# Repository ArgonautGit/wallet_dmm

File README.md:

# wallet_dmm

A multimeter the size of a credit card: DC volts, resistance, continuity and
diode test, shown on a 0.91" OLED, with three buttons, an RGB LED and a piezo
beeper. It runs from a small LiPo that charges over USB-C and is built around
an STM32L051K8, with Rust firmware and a simulation of the whole thing.

This is revision 3. Rev 1 (the October 2024 JLCPCB order) is commit `a01ea68`;
rev 2 is the `v2` branch.

| | |
|---|---|
| Inputs | COM, V (10 MΩ) and Ω (resistance, continuity, diode) on a 2.54 mm header |
| Voltage | −30 V to +31 V; negative readings through a 1.55 V mid-rail bias |
| Resistance | 0–200 kΩ against a 0.1 % 10 kΩ reference, 150 kΩ–10 MΩ against 1 MΩ, autoranging |
| Continuity, diode | 0.3 mA test current, open-circuit 3.0 V |
| Overload | both inputs survive ±30 V DC; not for mains or anything above 30 V |
| Power | 3.7 V LiPo (protected cell), 100 mA USB-C charging, 3.0 V rail, about 5 µA off |
| Board | 85.6 × 54 mm (ID-1 card), 2 layers, 0.8 mm FR4 |

## Changes from rev 1 and rev 2

- **Power.** The CR1025 (rated 0.1 mA continuous) could not run an OLED. It is
  replaced by a LiPo charged from USB-C (MCP73831), a 1 µA 3.0 V LDO that
  stays on while the MCU sleeps in Stop mode, a slide switch that disconnects
  the battery, bulk decoupling, and a load switch (Q1/Q2) that cuts the OLED
  module's supply.
- **Piezo.** The always-running 555 and its two MOSFETs are gone. The MCU
  drives the piezo push-pull from TIM22 CH1/CH2 on PB4/PB5, which gives
  6 Vp-p from 3 V and draws nothing when silent.
- **Programming.** SWD is on PA13/PA14 with NRST, with nothing else on those
  pins. USART1 (PA9/PA10, also the ROM bootloader) is on test pads.
- **Measurement.** Separate V and Ω inputs. The V input is a 9.87 MΩ divider
  biased to a mid-rail reference, with a hold capacitor because the ADC wants
  a source below 50 kΩ. The Ω input has two reference ranges; its drive nodes
  are clamped to ground and the battery, so a voltage on it pushes at most
  2.5 mA into the cell instead of into the MCU or the 3.0 V rail. What the
  MCU pins' own clamps still pass would lift the rail while the MCU sleeps
  (the LDO cannot sink current), so a TL431 (U4) holds it below 3.32 V.
- **Everything else.** A resistor for each LED colour, with the anode on the
  battery so green and blue have headroom. The MCU's calibrated internal
  sensor replaces the TO-92 MCP9700. Decoupling sits at the pins. Every part
  is stocked by JLCPCB and carries its LCSC number. All libraries are in the
  repo.

## Layout of the repository

- `hardware/`: KiCad 10 project (schematic, board, project rules, footprints
  for the RGB LED and the OLED module, 3D models for every part)
- `scripts/`: generators for the schematic, board and 3D models, the
  autorouter wrapper, the fab-file export and the renders
- `fab/`: Gerbers, drill files, BOM and pick-and-place for JLCPCB, schematic
  and assembly PDFs
- `firmware/`: Rust firmware and its simulation (see
  [firmware/README.md](firmware/README.md))
- `docs/`: renders of the board and the simulation results

## Building

Everything runs in the dev shell (`nix develop`, or direnv).

```sh
./scripts/build.sh          # schematic -> ERC -> board -> DRC -> fab/
```

The schematic and board are generated by `scripts/gen_schematic.py` and
`scripts/gen_pcb.py`; edit those rather than the KiCad files, or the next
build will overwrite the change. Tracks come from `hardware/routes.json`.
After moving parts or changing the netlist, route again with Freerouting:

```sh
kicad-cli sch export netlist --format kicadsexpr -o build/wallet_dmm.net hardware/wallet_dmm.kicad_sch
python3 scripts/autoroute.py build/wallet_dmm.net
```

The build stops on any ERC or DRC error and checks that the board matches the
schematic.

The renders in `docs/renders/` and a GLB of the populated board
(`build/wallet_dmm.glb`, for any glTF viewer) come from:

```sh
./scripts/render.sh
```

Most parts use KiCad's own 3D models; the switches, buzzer, USB-C socket and
RGB LED use the manufacturers' models (via EasyEDA). The OLED module and the
battery are drawn by `scripts/gen_models.py`, which lights the OLED's pixels
with the firmware's volts screen:

```sh
nix develop .#models -c uv run --with cadquery python scripts/gen_models.py
```

## Ordering from JLCPCB

Upload `fab/wallet_dmm-gerbers.zip`: 2 layers, **0.8 mm**, 1 oz, any colour,
HASL lead-free or ENIG. For assembly, choose top side and upload
`fab/bom-jlcpcb.csv` and `fab/cpl-jlcpcb.csv`. In the placement preview,
check the orientation of U1 (pin 1 dot), U2, U3, Q1, Q2, D2, D3, D1 (cathode)
and D4 (anode corner, the dot in the silkscreen) before confirming.

Solder these by hand afterwards:

- J3: a 0.91" 128×32 SSD1306 I2C module, flat on the board, header pins cut
  short. Match the module's pin labels to the silkscreen (GND VCC SCL SDA).
- J2: a 3-pin header or the probe leads (COM, V, Ω).
- J5: the battery wires from the back, BAT+ to the square pad.
- J4 stays empty; hold a header in it for an ST-Link, or solder one while
  developing.

## Battery

A LiPo pouch cell with its own protection circuit, up to 30 × 40 × 4 mm,
taped to the marked area on the back (no pins poke through there). Charging
runs at 100 mA, so use 150 mAh or more; R3 sets the current (1000 V / R3).

## Bring-up

1. Before connecting anything, check that BAT and 3V0 (TP3, TP4) are not
   shorted to GND.
2. Connect the battery and slide SW5 to ON. TP4 reads 2.94–3.06 V. If it
   reads 0 V, the switch is the other way round from the silkscreen: fix the
   labels in `scripts/gen_pcb.py`.
3. Plug in USB-C: the CHG LED lights while the cell charges and goes out when
   it is full.
4. Flash over SWD (ST-Link on J4: 3V0, SWDIO, SWCLK, NRST, GND). Holding
   RESET while connecting works if firmware has put the MCU to sleep.
5. With the firmware running ([firmware/README.md](firmware/README.md)):
   short V to COM in DC V and hold C for 3 s to store the zero; do the same
   with the Ω leads in Ω mode. Then put 5–30 V on the V input, measure it with another
   meter, and send `cal <volts>` over the UART (TP2) to set the gain.

## Firmware

The firmware is in [firmware/](firmware/): Rust and Embassy, with all the
maths and the UI in a host-tested crate. Its README covers the buttons,
calibration, flashing and the simulation. The pins:

| Pin | Use |
|---|---|
| PA0 ADC_IN0 | E_LO: the low-range drive node, through R18 |
| PA1 ADC_IN1 | VMID, the bias under the V divider |
| PA2 | VMID_EN: high while measuring volts |
| PA3 | OHM_HI: high-range drive (1 MΩ), analog otherwise |
| PA4 ADC_IN4 | V input divider |
| PA5 ADC_IN5 | Ω input, through R21 into C13 |
| PA6 | OHM_LO: low-range drive (10 kΩ), analog otherwise |
| PA7 | VBUS present (high on USB) |
| PB1 ADC_IN9 | switched battery ÷ 2 |
| PA8, PA15, PB3 | LED blue, red, green (low = on; PA15/PB3 are TIM2 CH1/CH2) |
| PB4, PB5 | piezo, TIM22 CH1/CH2 in antiphase, about 4 kHz |
| PB6, PB7 | I2C1 to the OLED (address 0x3C) |
| PC15 | OLED power: high = on |
| PA11, PA12, PC14 | buttons A, B, C to GND (enable pull-ups) |
| PA9, PA10 | USART1 TX/RX on TP1/TP2 |

## Simulation

`firmware/simulate.sh` runs the front end in ngspice, feeds it through a
model of the ADC into the firmware's own maths, and runs the release binary
in Renode on an emulated STM32L051. Across 200 simulated boards with 1 %
parts, calibrated volts are within ±4 mV up to ±5 V and ±33 mV at ±30 V,
and ohms within ±0.34 % from 1 kΩ to 100 kΩ. The details and plots are in
[firmware/README.md](firmware/README.md#simulation) and
[docs/simulation/](docs/simulation/).

## Renders

| Front | Back, with the battery |
|---|---|
|  |  |

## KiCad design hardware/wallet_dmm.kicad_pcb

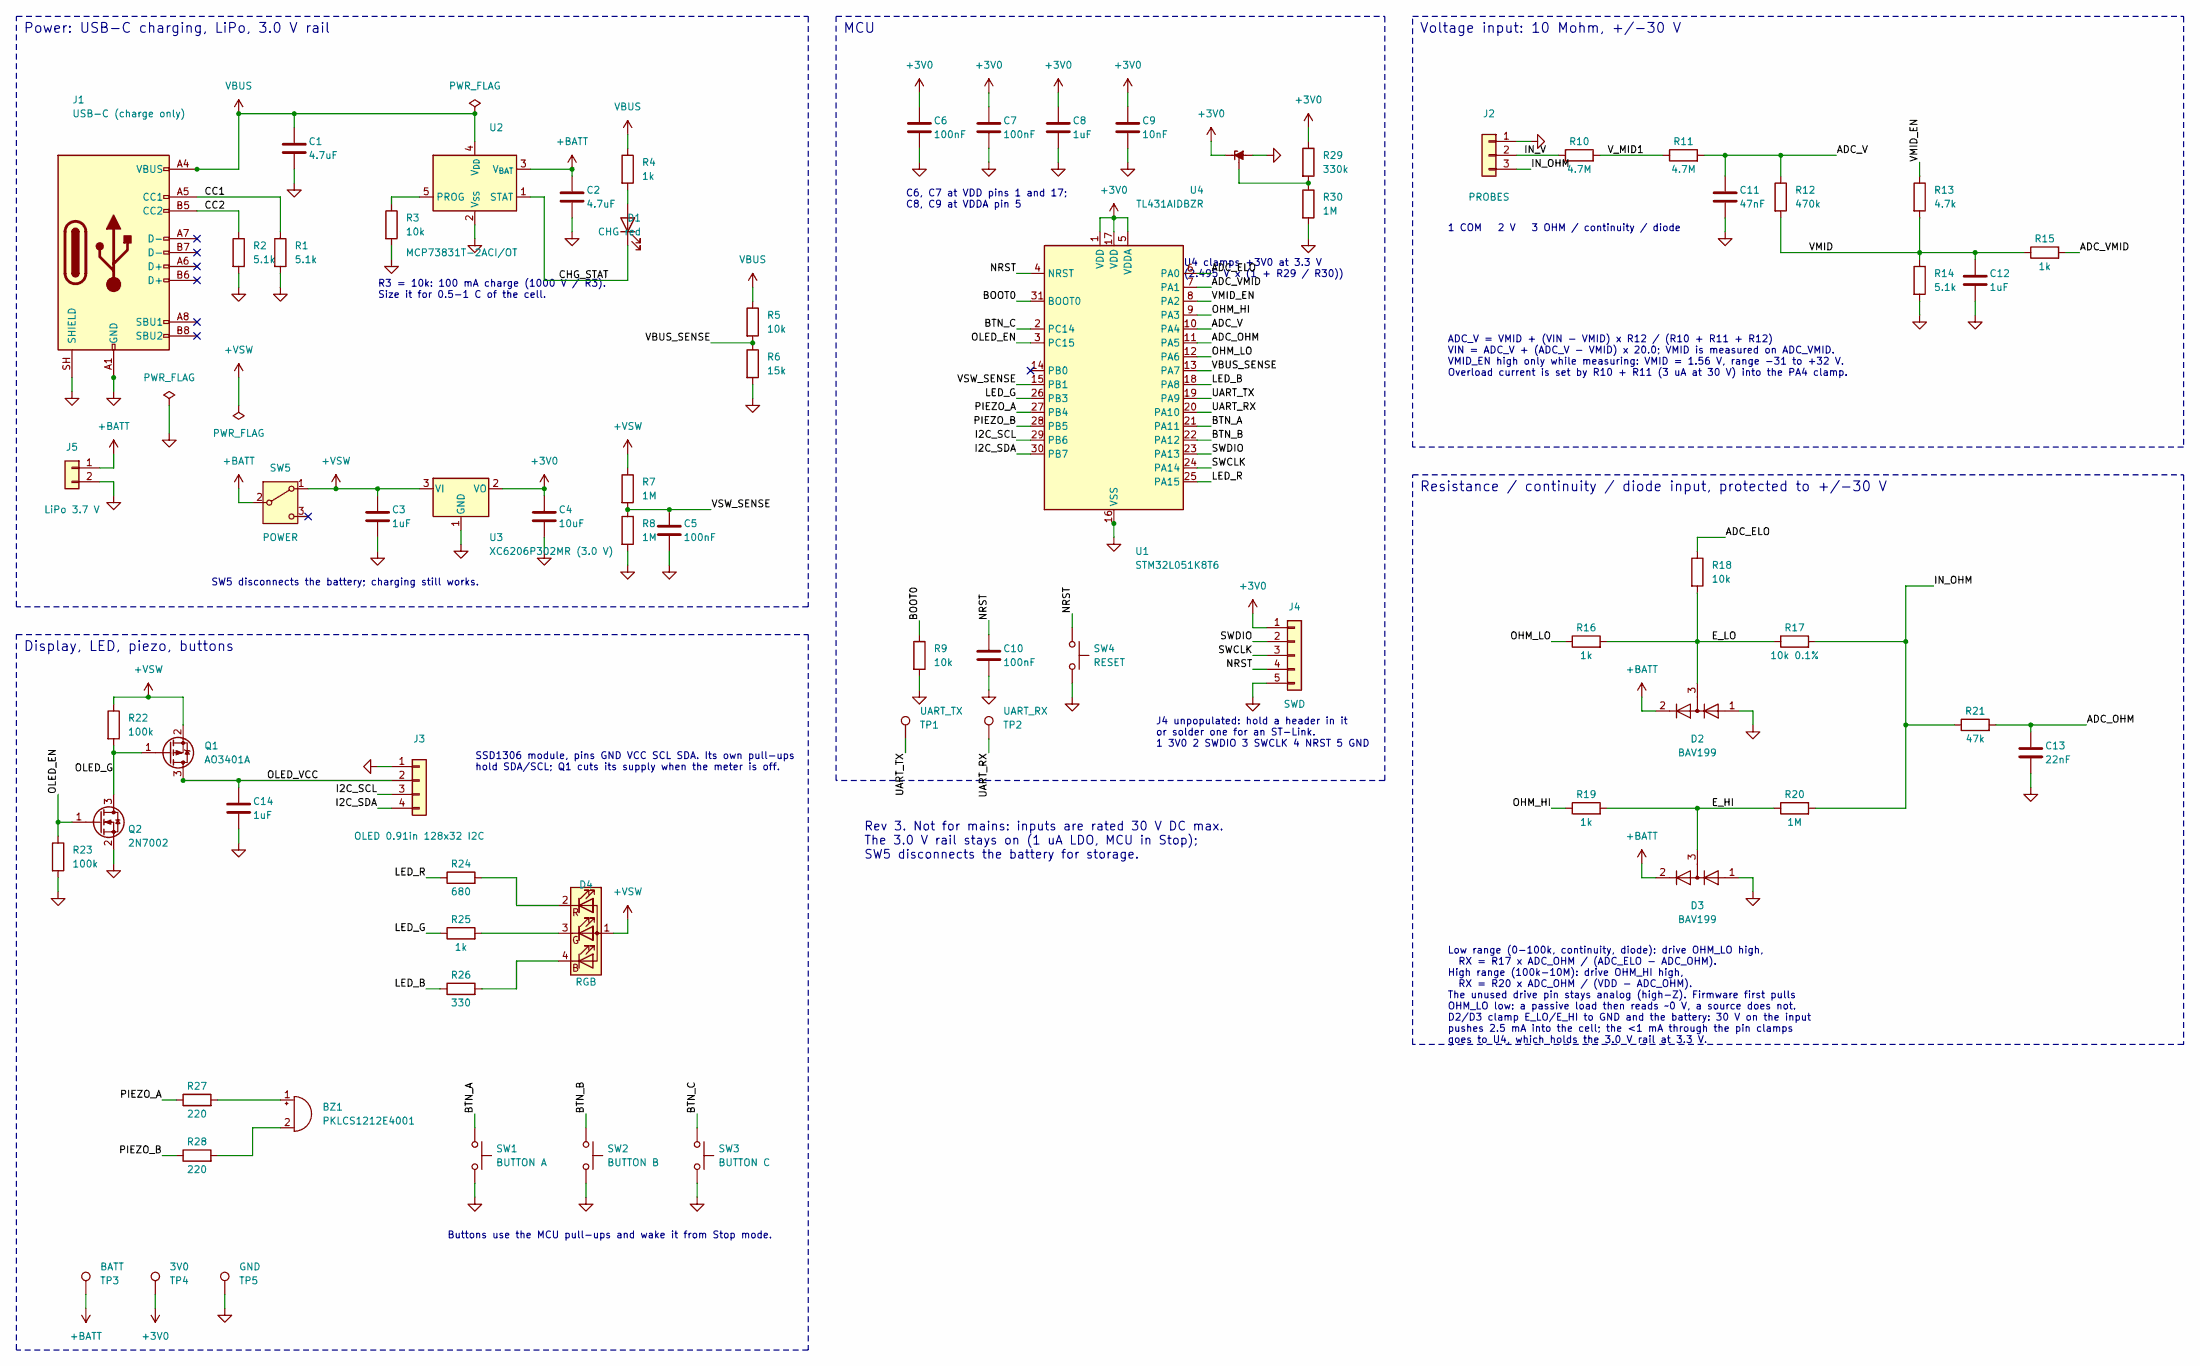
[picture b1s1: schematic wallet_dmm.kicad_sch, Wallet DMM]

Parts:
BZ1: PKLCS1212E4001; Buzzer_Murata_PKLCS1212E; MPN PKLCS1212E4001-R1; LCSC C113159
C1, C2: 4.7uF; C_0603_1608Metric; MPN CL10A475KO8NNNC; LCSC C19666
C3, C8, C12, C14: 1uF; C_0603_1608Metric; MPN CL10A105KB8NNNC; LCSC C15849
C4: 10uF; C_0603_1608Metric; MPN CL10A106KP8NNNC; LCSC C19702
C5, C6, C7, C10: 100nF; C_0603_1608Metric; MPN CC0603KRX7R9BB104; LCSC C14663
C9: 10nF; C_0603_1608Metric; MPN 0603B103K500NT; LCSC C57112
C11: 47nF; C_0603_1608Metric; MPN CL10B473KB8NNNC; LCSC C1622
C13: 22nF; C_0603_1608Metric; MPN CL10B223KB8NNNC; LCSC C21122
D1: CHG red; LED_0603_1608Metric; MPN KT-0603R; LCSC C2286
D2, D3: BAV199; SOT-23; MPN BAV199,215; LCSC C40919
D4: RGB; LED_RGB_1615_CA; MPN TJ-S1615CY6TGLCCYRGB-A5; LCSC C601683
J1: USB-C (charge only); USB_C_Receptacle_HRO_TYPE-C-31-M-12; MPN TYPE-C-31-M-12; LCSC C165948
J2: PROBES; PinHeader_1x03_P2.54mm_Vertical
J3: OLED 0.91in 128x32 I2C; OLED_0.91in_128x32_Module
J4: SWD; PinHeader_1x05_P2.54mm_Vertical
J5: LiPo 3.7 V; SolderWire-0.25sqmm_1x02_P4.5mm_D0.65mm_OD2mm
Q1: AO3401A; SOT-23; MPN AO3401A; LCSC C15127
Q2: 2N7002; SOT-23; MPN 2N7002; LCSC C8545
R1, R2, R14: 5.1k; R_0603_1608Metric; MPN 0603WAF5101T5E; LCSC C23186
R3, R5, R9, R18: 10k; R_0603_1608Metric; MPN 0603WAF1002T5E; LCSC C25804
R4, R15, R16, R19, R25: 1k; R_0603_1608Metric; MPN 0603WAF1001T5E; LCSC C21190
R6: 15k; R_0603_1608Metric; MPN 0603WAF1502T5E; LCSC C22809
R7, R8, R20, R30: 1M; R_0603_1608Metric; MPN 0603WAF1004T5E; LCSC C22935
R10, R11: 4.7M; R_1206_3216Metric; MPN 1206W4F4704T5E; LCSC C37800
R12: 470k; R_0603_1608Metric; MPN 0603WAF4703T5E; LCSC C23178
R13: 4.7k; R_0603_1608Metric; MPN 0603WAF4701T5E; LCSC C23162
R17: 10k 0.1%; R_1206_3216Metric; MPN RT1206BRD0710KL; LCSC C136889
R21: 47k; R_0603_1608Metric; MPN 0603WAF4702T5E; LCSC C25819
R22, R23: 100k; R_0603_1608Metric; MPN 0603WAF1003T5E; LCSC C25803
R24: 680; R_0603_1608Metric; MPN 0603WAF6800T5E; LCSC C23228
R26: 330; R_0603_1608Metric; MPN 0603WAF3300T5E; LCSC C23138
R27, R28: 220; R_0603_1608Metric; MPN 0603WAF2200T5E; LCSC C22962
R29: 330k; R_0603_1608Metric; MPN 0603WAF3303T5E; LCSC C23137
SW1: BUTTON A; SW_Push_1P1T_XKB_TS-1187A; MPN TS-1187A-B-A-B; LCSC C318884
SW2: BUTTON B; SW_Push_1P1T_XKB_TS-1187A; MPN TS-1187A-B-A-B; LCSC C318884
SW3: BUTTON C; SW_Push_1P1T_XKB_TS-1187A; MPN TS-1187A-B-A-B; LCSC C318884
SW4: RESET; SW_Push_1P1T_XKB_TS-1187A; MPN TS-1187A-B-A-B; LCSC C318884
SW5: POWER; SW_SPDT_Shouhan_MSK12C02; MPN MSK12C02; LCSC C431540
TP1: UART_TX; TestPoint_Pad_D1.5mm
TP2: UART_RX; TestPoint_Pad_D1.5mm
TP3: BATT; TestPoint_Pad_D1.5mm
TP4: 3V0; TestPoint_Pad_D1.5mm
TP5: GND; TestPoint_Pad_D1.5mm
U1: STM32L051K8T6; LQFP-32_7x7mm_P0.8mm; MPN STM32L051K8T6; LCSC C915970
U2: MCP73831T-2ACI/OT; SOT-23-5; MPN MCP73831T-2ACI/OT; LCSC C424093
U3: XC6206P302MR (3.0 V); SOT-23-3; MPN XC6206P302MR-G; LCSC C9972
U4: TL431AIDBZR; SOT-23; MPN TL431AIDBZR; LCSC C23892

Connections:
+3V0: C4.1, C6.1, C7.1, C8.1, C9.1, J4.1, R29.1, TP4.1, U1.1 (VDD), U1.5 (VDDA), U1.17 (VDD), U3.2 (VO), U4.1 (K)
+BATT: C2.1, D2.2 (A), D3.2 (A), J5.1, SW5.2 (B), TP3.1, U2.3 (V_{BAT})
+VSW: C3.1, D4.1 (A), Q1.2 (S), R7.1, R22.1, SW5.1 (A), U3.3 (VI)
/ADC_ELO: R18.1, U1.6 (PA0)
/ADC_OHM: C13.1, R21.2, U1.11 (PA5)
/ADC_V: C11.1, R11.2, R12.1, U1.10 (PA4)
/ADC_VMID: R15.2, U1.7 (PA1)
/BOOT0: R9.1, U1.31 (BOOT0)
/BTN_A: SW1.1, U1.21 (PA11)
/BTN_B: SW2.1, U1.22 (PA12)
/BTN_C: SW3.1, U1.2 (PC14)
/CC1: J1.A5 (CC1), R1.1
/CC2: J1.B5 (CC2), R2.1
/CHG_STAT: D1.1 (K), U2.1 (STAT)
/E_HI: D3.3 (K), R19.2, R20.1
/E_LO: D2.3 (K), R16.2, R17.1, R18.2
/I2C_SCL: J3.3, U1.29 (PB6)
/I2C_SDA: J3.4, U1.30 (PB7)
/IN_OHM: J2.3, R17.2, R20.2, R21.1
/IN_V: J2.2, R10.1
/LED_B: R26.1, U1.18 (PA8)
/LED_G: R25.1, U1.26 (PB3)
/LED_R: R24.1, U1.25 (PA15)
/NRST: C10.1, J4.4, SW4.1, U1.4 (NRST)
/OHM_HI: R19.1, U1.9 (PA3)
/OHM_LO: R16.1, U1.12 (PA6)
/OLED_EN: Q2.1 (G), R23.1, U1.3 (PC15)
/OLED_G: Q1.1 (G), Q2.3 (D), R22.2
/OLED_VCC: C14.1, J3.2, Q1.3 (D)
/PIEZO_A: R27.1, U1.27 (PB4)
/PIEZO_B: R28.1, U1.28 (PB5)
/SWCLK: J4.3, U1.24 (PA14)
/SWDIO: J4.2, U1.23 (PA13)
/UART_RX: TP2.1, U1.20 (PA10)
/UART_TX: TP1.1, U1.19 (PA9)
/VBUS_SENSE: R5.2, R6.1, U1.13 (PA7)
/VMID: C12.1, R12.2, R13.2, R14.1, R15.1
/VMID_EN: R13.1, U1.8 (PA2)
/VSW_SENSE: C5.1, R7.2, R8.1, U1.15 (PB1)
/V_MID1: R10.2, R11.1
GND: C1.2, C2.2, C3.2, C4.2, C5.2, C6.2, C7.2, C8.2, C9.2, C10.2, C11.2, C12.2, C13.2, C14.2, D2.1 (K), D3.1 (K), J1.A1 (GND), J1.A12 (GND), J1.B1 (GND), J1.B12 (GND), J1.SH (SHIELD), J2.1, J3.1, J4.5, J5.2, Q2.2 (S), R1.2, R2.2, R3.2, R6.2, R8.2, R9.2, R14.2, R23.2, R30.2, SW1.2, SW2.2, SW3.2, SW4.2, TP5.1, U1.16 (VSS), U1.32 (VSS), U2.2 (V_{SS}), U3.1 (GND), U4.3 (A)
unnamed: BZ1.1 (+), R27.2
unnamed: BZ1.2 (-), R28.2
unnamed: D1.2 (A), R4.2
unnamed: D4.4 (BK), R26.2
unnamed: D4.3 (GK), R25.2
unnamed: D4.2 (RK), R24.2
unnamed: R3.1, U2.5 (PROG)
unnamed: R29.2, R30.1, U4.2 (REF)
VBUS: C1.1, J1.A4 (VBUS), J1.A9 (VBUS), J1.B4 (VBUS), J1.B9 (VBUS), R4.1, R5.1, U2.4 (V_{DD})

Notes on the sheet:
ADC_V = VMID + (VIN - VMID) x R12 / (R10 + R11 + R12) VIN = ADC_V + (ADC_V - VMID) x 20.0; VMID is measured on ADC_VMID. VMID_EN high only while measuring: VMID = 1.56 V, range -31 to +32 V. Overload current is set by R10 + R11 (3 uA at 30 V) into the PA4 clamp.
C6, C7 at VDD pins 1 and 17; C8, C9 at VDDA pin 5
J4 unpopulated: hold a header in it or solder one for an ST-Link. 1 3V0 2 SWDIO 3 SWCLK 4 NRST 5 GND
Power: USB-C charging, LiPo, 3.0 V rail
Voltage input: 10 Mohm, +/-30 V
R3 = 10k: 100 mA charge (1000 V / R3). Size it for 0.5-1 C of the cell.
Buttons use the MCU pull-ups and wake it from Stop mode.
Display, LED, piezo, buttons
Resistance / continuity / diode input, protected to +/-30 V
SSD1306 module, pins GND VCC SCL SDA. Its own pull-ups hold SDA/SCL; Q1 cuts its supply when the meter is off.
Rev 3. Not for mains: inputs are rated 30 V DC max. The 3.0 V rail stays on (1 uA LDO, MCU in Stop); SW5 disconnects the battery for storage.
Low range (0-100k, continuity, diode): drive OHM_LO high, RX = R17 x ADC_OHM / (ADC_ELO - ADC_OHM). High range (100k-10M): drive OHM_HI high, RX = R20 x ADC_OHM / (VDD - ADC_OHM). The unused drive pin stays analog (high-Z). Firmware first pulls OHM_LO low: a passive load then reads ~0 V, a source d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
SW5 disconnects the battery; charging still works.
1 COM 2 V 3 OHM / continuity / diode
U4 clamps +3V0 at 3.3 V (2.495 V x (1 + R29 / R30))
MCU

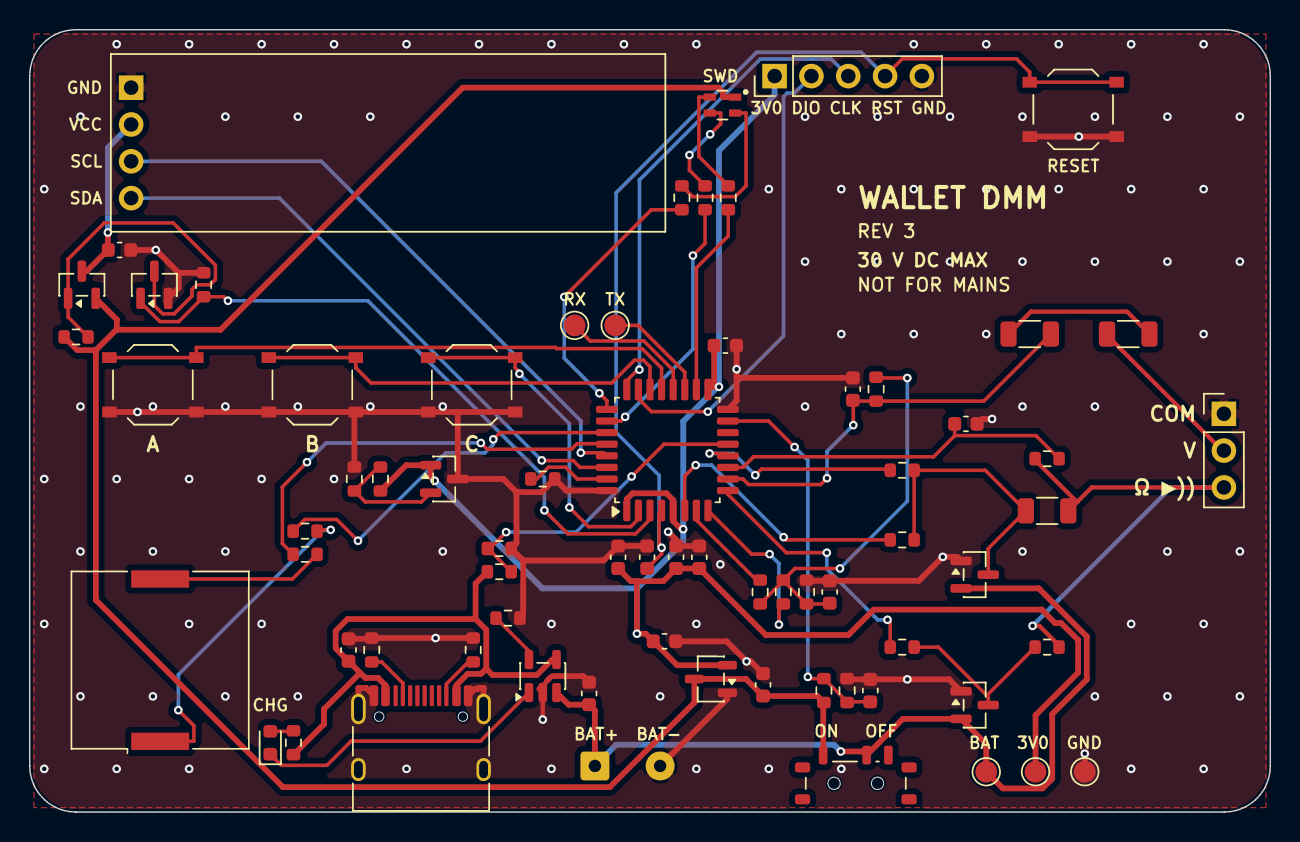
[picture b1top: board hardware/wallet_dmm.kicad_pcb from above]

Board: 2 copper layers, 85.6 x 54.0 mm, 70 parts (0 on the bottom side), 50 nets.

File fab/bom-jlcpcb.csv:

Comment,Designator,Footprint,LCSC Part #
PKLCS1212E4001,BZ1,Buzzer_Murata_PKLCS1212E,C113159
4.7uF,"C1,C2",C_0603_1608Metric,C19666
1uF,"C3,C8,C12,C14",C_0603_1608Metric,C15849
10uF,C4,C_0603_1608Metric,C19702
100nF,"C5,C6,C7,C10,C13",C_0603_1608Metric,C14663
10nF,C9,C_0603_1608Metric,C57112
47nF,C11,C_0603_1608Metric,C1622
CHG red,D1,LED_0603_1608Metric,C2286
BAV199,"D2,D3",SOT-23,C40919
RGB,D4,LED_RGB_1615_CA,C601683
USB-C (charge only),J1,USB_C_Receptacle_HRO_TYPE-C-31-M-12,C165948
AO3401A,Q1,SOT-23,C15127
2N7002,Q2,SOT-23,C8545
5.1k,"R1,R2",R_0603_1608Metric,C23186
10k,"R3,R5,R9,R13,R14,R18",R_0603_1608Metric,C25804
1k,"R4,R15,R16,R19,R25",R_0603_1608Metric,C21190
15k,R6,R_0603_1608Metric,C22809
1M,"R7,R8,R20",R_0603_1608Metric,C22935
4.7M,"R10,R11",R_1206_3216Metric,C37800
470k,R12,R_0603_1608Metric,C23178
10k 0.1%,R17,R_1206_3216Metric,C136889
47k,R21,R_0603_1608Metric,C25819
100k,"R22,R23",R_0603_1608Metric,C25803
680,R24,R_0603_1608Metric,C23228
330,R26,R_0603_1608Metric,C23138
220,"R27,R28",R_0603_1608Metric,C22962
BUTTON A,SW1,SW_Push_1P1T_XKB_TS-1187A,C318884
BUTTON B,SW2,SW_Push_1P1T_XKB_TS-1187A,C318884
BUTTON C,SW3,SW_Push_1P1T_XKB_TS-1187A,C318884
RESET,SW4,SW_Push_1P1T_XKB_TS-1187A,C318884
POWER,SW5,SW_SPDT_Shouhan_MSK12C02,C431540
STM32L051K8T6,U1,LQFP-32_7x7mm_P0.8mm,C915970
MCP73831T-2ACI/OT,U2,SOT-23-5,C424093
XC6206P302MR (3.0 V),U3,SOT-23-3,C9972

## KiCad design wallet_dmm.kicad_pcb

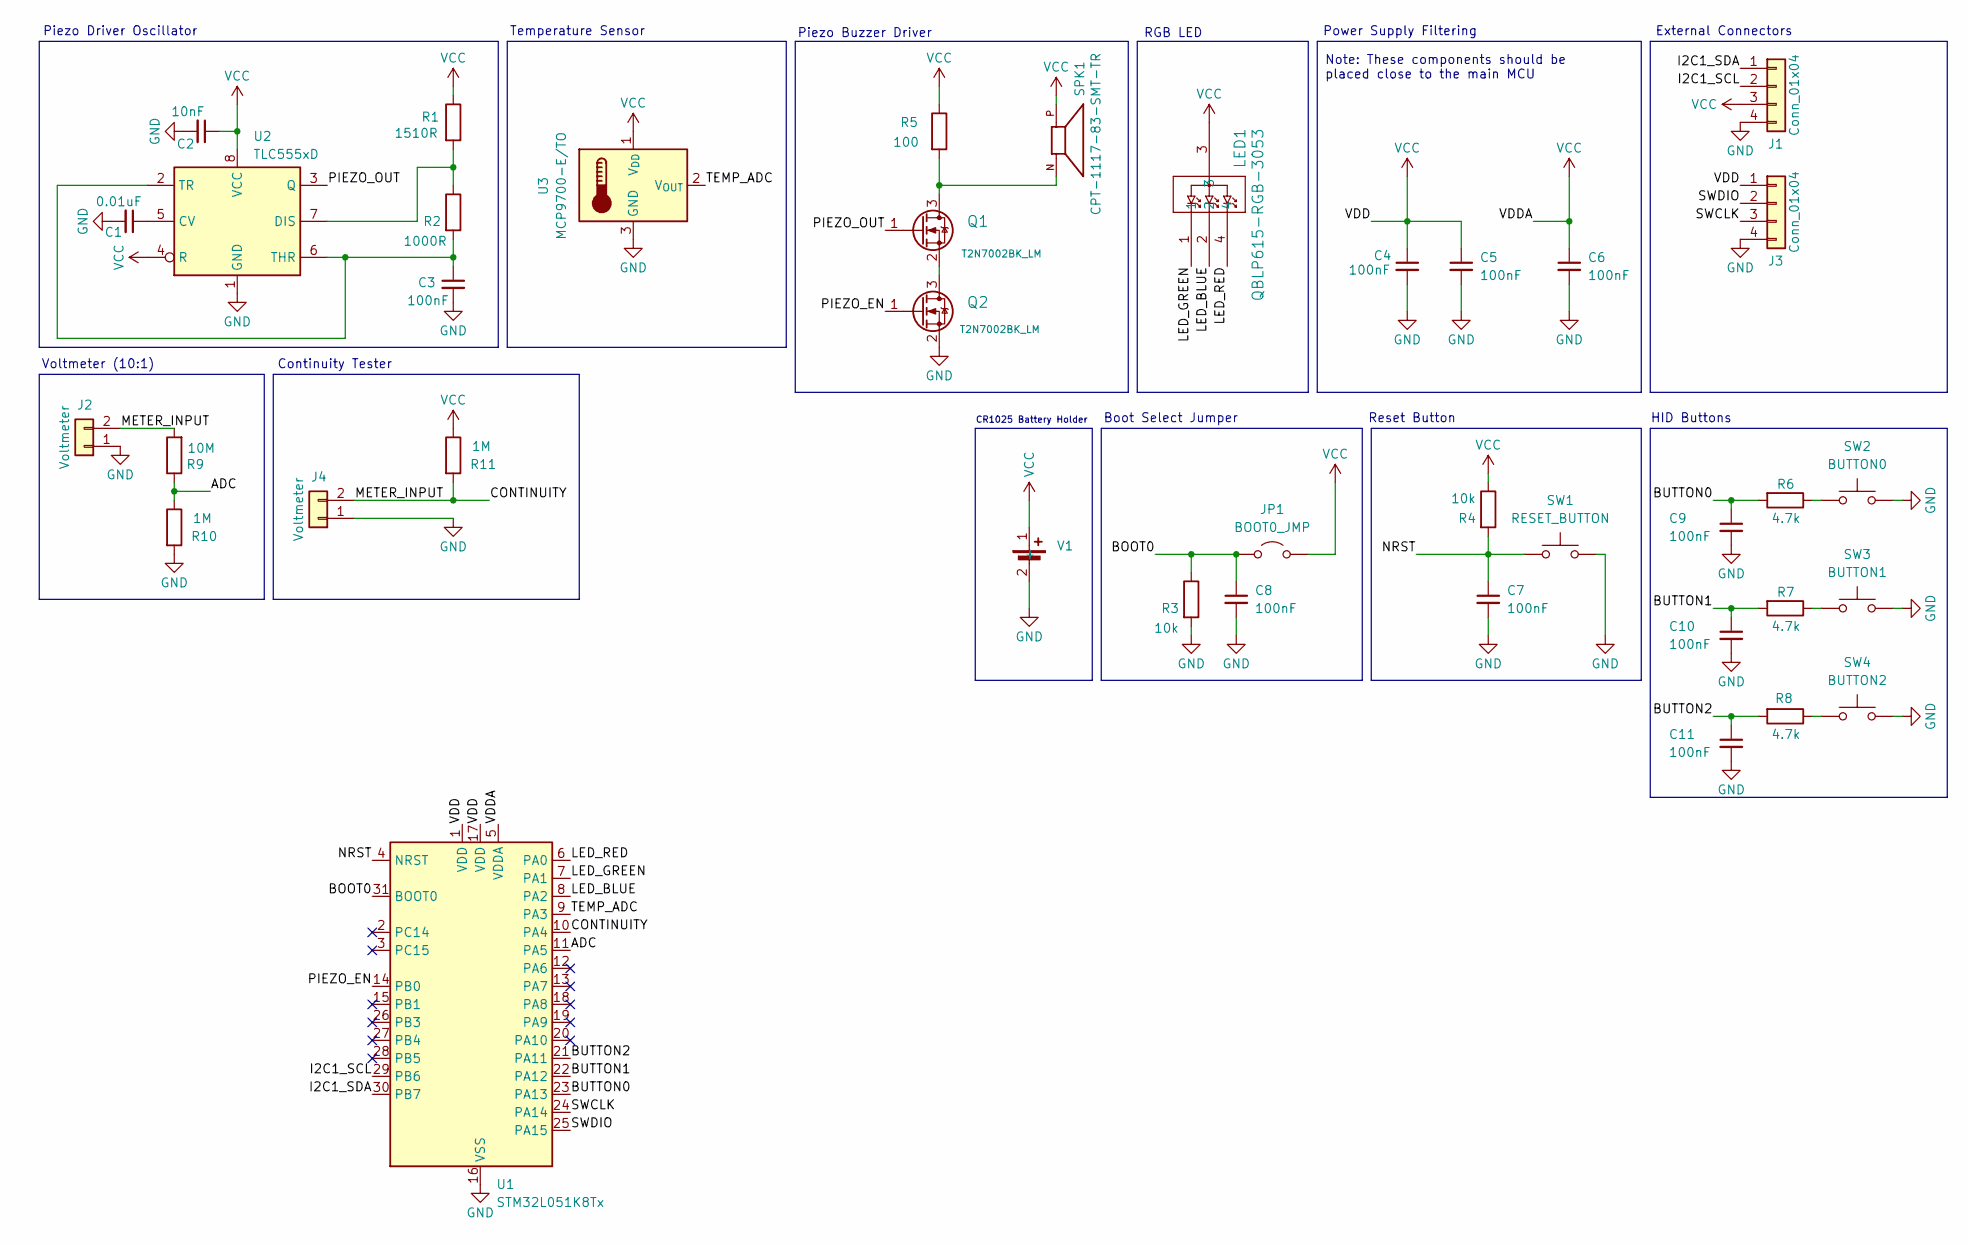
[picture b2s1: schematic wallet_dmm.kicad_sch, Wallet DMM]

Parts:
C1: 0.01uF; C_0603_1608Metric_Pad1.08x0.95mm_HandSolder
C2: 10nF; C_0603_1608Metric_Pad1.08x0.95mm_HandSolder
C3, C4, C5, C6, C7, C8, C9, C10, C11: 100nF; C_0603_1608Metric_Pad1.08x0.95mm_HandSolder
J1: Conn_01x04; OLED_Header
J2, J4: Voltmeter; PinHeader_1x02_P2.54mm_Vertical
J3: Conn_01x04; PinHeader_1x04_P2.54mm_Vertical
JP1: BOOT0_JMP; SolderJumper-2_P1.3mm_Open_RoundedPad1.0x1.5mm
LED1: QBLP615-RGB-3053; QBLP615-RGB-3053_QTB
Q1, Q2: T2N7002BK_LM; T2N7002BK
R1: 1510R; R_0603_1608Metric_Pad0.98x0.95mm_HandSolder
R2: 1000R; R_0603_1608Metric_Pad0.98x0.95mm_HandSolder
R3, R4: 10k; R_0603_1608Metric_Pad0.98x0.95mm_HandSolder
R5: 100; R_0603_1608Metric_Pad0.98x0.95mm_HandSolder
R6, R7, R8: 4.7k; R_0603_1608Metric_Pad0.98x0.95mm_HandSolder
R9: 10M; R_0603_1608Metric_Pad0.98x0.95mm_HandSolder
R10, R11: 1M; R_0603_1608Metric_Pad0.98x0.95mm_HandSolder
SPK1: CPT-1117-83-SMT-TR; XDCR_CPT-1117-83-SMT-TR; PARTREV N/A
SW1: RESET_BUTTON; SW4_PTS815 SJM 250 SMTR LFS_CNK
SW2: BUTTON0; SW4_PTS815 SJM 250 SMTR LFS_CNK
SW3: BUTTON1; SW4_PTS815 SJM 250 SMTR LFS_CNK
SW4: BUTTON2; SW4_PTS815 SJM 250 SMTR LFS_CNK
U1: STM32L051K8Tx; LQFP-32_7x7mm_P0.8mm
U2: TLC555xD; SOIC-8_3.9x4.9mm_P1.27mm
U3: MCP9700-E/TO; TO-92L_Inline
V1: BK-870-TR

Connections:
/ADC: R9.1, R10.1, U1.11 (PA5)
/BOOT0: C8.1, JP1.1 (A), R3.1, U1.31 (BOOT0)
/BUTTON0: C9.1, R6.2, U1.23 (PA13)
/BUTTON1: C10.1, R7.2, U1.22 (PA12)
/BUTTON2: C11.1, R8.2, U1.21 (PA11)
/CONTINUITY: J2.2, J4.2, R9.2, R11.2, U1.10 (PA4)
/I2C1_SCL: J1.2, U1.29 (PB6)
/I2C1_SDA: J1.1, U1.30 (PB7)
/LED_BLUE: LED1.2, U1.8 (PA2)
/LED_GREEN: LED1.1, U1.7 (PA1)
/LED_RED: LED1.4, U1.6 (PA0)
/NRST: C7.1, R4.2, SW1.1 (A), SW1.2 (A), U1.4 (NRST)
/PIEZO_EN: Q2.1 (G), U1.14 (PB0)
/PIEZO_OUT: Q1.1 (G), U2.3 (Q)
/SWCLK: J3.3, U1.24 (PA14)
/SWDIO: J3.2, U1.25 (PA15)
/TEMP_ADC: U1.9 (PA3), U3.2 (V_{OUT})
GND: C1.2, C2.2, C3.2, C4.2, C5.2, C6.2, C7.2, C8.2, C9.2, C10.2, C11.2, J1.4, J2.1, J3.4, J4.1, Q2.2 (S), R3.2, R10.2, SW1.3 (B), SW1.4 (B), SW2.3 (B), SW2.4 (B), SW3.3 (B), SW3.4 (B), SW4.3 (B), SW4.4 (B), U1.16 (VSS), U1.32 (VSS), U2.1 (GND), U3.3 (GND), V1.2 (-)
unnamed: Q1.3 (D), R5.2, SPK1.N
unnamed: Q1.2 (S), Q2.3 (D)
unnamed: R6.1, SW2.1 (A), SW2.2 (A)
unnamed: R7.1, SW3.1 (A), SW3.2 (A)
unnamed: R8.1, SW4.1 (A), SW4.2 (A)
unnamed: C1.1, U2.5 (CV)
unnamed: R1.2, R2.1, U2.7 (DIS)
unnamed: C3.1, R2.2, U2.2 (TR), U2.6 (THR)
VCC: C2.1, C4.1, C5.1, C6.1, J1.3, J3.1, JP1.2 (B), LED1.3, R1.1, R4.1, R5.1, R11.1, SPK1.P, U1.1 (VDD), U1.5 (VDDA), U1.17 (VDD), U2.4 (R), U2.8 (VCC), U3.1 (V_{DD}), V1.1 (+)

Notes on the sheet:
External Connectors
Voltmeter (10:1)
Temperature Sensor
Piezo Driver Oscillator
Boot Select Jumper
Reset Button
Piezo Buzzer Driver
CR1025 Battery Holder
RGB LED
HID Buttons
Note: These components should be placed close to the main MCU
Continuity Tester
Power Supply Filtering

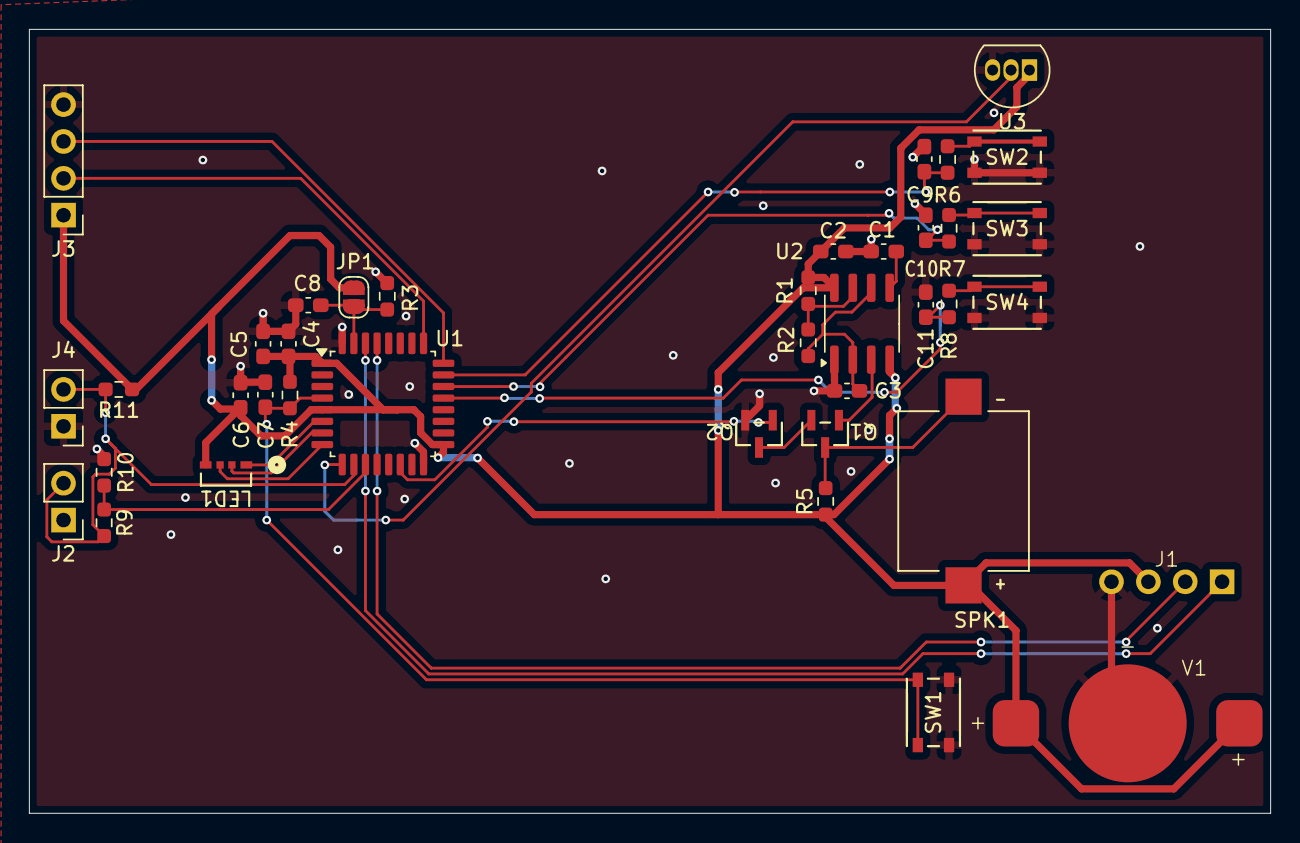
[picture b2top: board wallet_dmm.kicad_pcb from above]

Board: 2 copper layers, 85.5 x 54.0 mm, 39 parts (0 on the bottom side), 27 nets.

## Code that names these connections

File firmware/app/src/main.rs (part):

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            Mode::Info => (false, None),
        };
        self.vmid_en.set_level(if vmid { Level::High } else { Level::Low });
        for (pin, r) in [(&mut self.ohm_lo, Range::Low), (&mut self.ohm_hi, Range::High)] {
            if drive == Some(r) {
                pin.set_high();
                pin.set_as_output(Speed::Low);
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    let mut uart_config = usart::Config::default();
    uart_config.baudrate = 115_200;
    // `_rx` lives as long as main: dropping it would turn the receiver off.
    let (tx, _rx) = Uart::new_blocking(p.USART1, p.PA10, p.PA9, uart_config).unwrap().split();
    let mut log = Log(tx);
    log.line(&["wallet-dmm rev 3"]);
    unsafe {
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    spawner.spawn(commands().unwrap());

    let mut fe = FrontEnd {
        vmid_en: Output::new(p.PA2, Level::Low, Speed::Low),
        ohm_lo: Flex::new(p.PA6),
        ohm_hi: Flex::new(p.PA3),
    };
    fe.off();
    let vbus = Input::new(p.PA7, Pull::None);
    let mut leds = Leds {
        red: Output::new(p.PA15, Level::High, Speed::Low),
        green: Output::new(p.PB3, Level::High, Speed::Low),
        blue: Output::new(p.PA8, Level::High, Speed::Low),
    };

    // Piezo: TIM22 CH1 and CH2 in antiphase at 4 kHz, 6 Vp-p across it.
    let mut piezo = SimplePwm::new(
        p.TIM22,
        Some(PwmPin::new(p.PB4, OutputType::PushPull)),
        Some(PwmPin::new(p.PB5, OutputType::PushPull)),
        None,
        None,
        Hertz(4_000),
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    piezo.ch2().set_polarity(OutputPolarity::ActiveLow);

    // OLED module: power it through Q1, then give its regulator time to start.
    let mut oled_en = Output::new(p.PC15, Level::High, Speed::Low);
    Timer::after_millis(50).await;
    let mut i2c_config = i2c::Config::default();
    i2c_config.frequency = Hertz(400_000);
    let i2c = I2c::new_blocking(p.I2C1, p.PB6, p.PB7, i2c_config);
    let mut display = Ssd1306::new(I2CDisplayInterface::new(i2c), DisplaySize128x32, DisplayRotation::Rotate0)
        .into_buffered_graphics_mode();
    let display_ok = display.init().is_ok();
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    let mut cal = eeprom::load().unwrap_or_default();

    let buttons = [
        (ExtiInput::new(p.PA11, p.EXTI11, Pull::Up, Irqs), Button::A, 1500),
        (ExtiInput::new(p.PA12, p.EXTI12, Pull::Up, Irqs), Button::B, 1500),
        (ExtiInput::new(p.PC14, p.EXTI14, Pull::Up, Irqs), Button::C, 3000),
    ];
    for (pin, which, long_ms) in buttons {
        spawner.spawn(button(pin, which, long_ms).unwrap());
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
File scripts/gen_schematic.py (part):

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                     ref_at=(127.0, 49.53, "left"), val_at=(127.0, 52.07, "left"))
        s.wire(r4["2"], d1["2"])
        s.wire(u2["1"], (109.22, 45.72), (109.22, 60.96), (124.46, 60.96), d1["1"])
        s.wlabel("CHG_STAT", (111.76, 60.96))
        s.text("R3 = 10k: 100 mA charge (1000 V / R3).\nSize it for 0.5-1 C of the cell.", (78.74, 60.96))

        # VBUS present -> PA7 (3.0 V at 5 V in).
        r5 = self.R("R5", "10k", 147.32, 68.58, {"1": "VBUS"})
        r6 = self.R("R6", "15k", 147.32, 76.2, {"2": "GND"})
        s.wire(r5["2"], (139.7, 72.39))
        s.label("VBUS_SENSE", (139.7, 72.39), (-1, 0))
        s.nets.setdefault("VBUS_SENSE", []).append("R5")

        # Battery, power switch, 3.0 V LDO.
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        c4 = self.C("C4", "10uF", 109.22, 104.14)
        s.wire(u3["2"], (109.22, 99.06), c4["1"])
        s.power("+3V0", (109.22, 99.06), (0, -1))
        # Switched battery -> PB1, halved.
        r7 = self.R("R7", "1M", 124.46, 99.06, {"1": "+VSW"})
        r8 = self.R("R8", "1M", 124.46, 106.68, {"2": "GND"})
        c5 = self.C("C5", "100nF", 132.08, 106.68)
        s.wire(r7["2"], (132.08, 102.87), c5["1"])
        s.wire((132.08, 102.87), (139.7, 102.87))
        s.label("VSW_SENSE", (139.7, 102.87), (1, 0))
        s.nets.setdefault("VSW_SENSE", []).append("R7")
        s.text("SW5 disconnects the battery; charging still works.", (48.26, 115.57))

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        r11 = self.R("R11", "4.7M", 317.5, y, rot=90, fp=R1206, fields=r47)
        s.wire(j["2"], r10["1"])
        s.wire(r10["2"], r11["1"])
        s.wlabel("IN_V", (288.29, y))
        s.wlabel("V_MID1", (303.53, y))
        c11 = self.C("C11", "47nF", 325.12, 45.72)
        r12 = self.R("R12", "470k", 335.28, 45.72)
        s.wire(r11["2"], (325.12, y), (335.28, y), (345.44, y))
        s.label("ADC_V", (345.44, y), (1, 0))
        s.nets.setdefault("ADC_V", []).append("R11")
        s.wire((325.12, y), c11["1"])
        s.wire((335.28, y), r12["1"])
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        s.wire(r13["2"], (360.68, ym), r14["1"])
        s.wire((360.68, ym), (370.84, ym), r15["1"])
        s.wire((370.84, ym), c12["1"])
        s.wlabel("VMID", (340.36, ym))
        s.text("ADC_V = VMID + (VIN - VMID) x R12 / (R10 + R11 + R12)\n"
               "VIN = ADC_V + (ADC_V - VMID) x 20.0; VMID is measured on ADC_VMID.\n"
               "VMID_EN high only while measuring: VMID = 1.56 V, range -31 to +32 V.\n"
               "Overload current is set by R10 + R11 (3 uA at 30 V) into the PA4 clamp.",
               (274.32, 71.12))

    # ------------------------------------------------------- ohms input
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        r18 = self.R("R18", "10k", 320.04, 114.3)
        s.wire(r18["2"], rows["LO"])
        s.wire(r18["1"], (320.04, 107.95), (325.12, 107.95))
        s.label("ADC_ELO", (325.12, 107.95), (1, 0))
        s.nets.setdefault("ADC_ELO", []).append("R18")
        # The input itself, sensed through R21 into a hold capacitor.
        s.wire((bus + 5.08, 116.84), (bus, 116.84), (bus, 127.0), (bus, 142.24), (bus, 157.48))
        s.label("IN_OHM", (bus + 5.08, 116.84), (1, 0))
        s.nets.setdefault("IN_OHM", []).append("bus")
        r21 = self.R("R21", "47k", 370.84, 142.24, rot=90)
        c13 = self.C("C13", "22nF", 381.0, 147.32)
        s.wire((bus, 142.24), r21["1"])
        s.wire(r21["2"], (381.0, 142.24), (391.16, 142.24))
        s.wire((381.0, 142.24), c13["1"])
        s.label("ADC_OHM", (391.16, 142.24), (1, 0))
        s.nets.setdefault("ADC_OHM", []).append("R21")
        s.wlabel("E_LO", (322.58, 127.0))
        s.wlabel("E_HI", (322.58, 157.48))
        s.text("Low range (0-100k, continuity, diode): drive OHM_LO high,\n"
               "  RX = R17 x ADC_OHM / (ADC_ELO - ADC_OHM).\n"
               "High range (100k-10M): drive OHM_HI high,\n"
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        r23 = self.R("R23", "100k", 20.32, 166.37, {"2": "GND"})
        s.wire(q2["1"], (20.32, 160.02), r23["1"])
        s.wire((20.32, 160.02), (20.32, 154.94))
        s.label("OLED_EN", (20.32, 154.94), (0, -1))
        s.nets.setdefault("OLED_EN", []).append("Q2")
        oled = s.place("J3", "Connector_Generic:Conn_01x04", "OLED 0.91in 128x32 I2C", 86.36, 152.4,
                       footprint="wallet_dmm:OLED_0.91in_128x32_Module", in_bom=False,
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        s.wire((53.34, 152.4), c14["1"])
        s.conn(oled, "1", "GND", bend=False)
        s.connect(oled, {"3": "I2C_SCL", "4": "I2C_SDA"})
        s.wlabel("OLED_VCC", (58.42, 152.4))
        s.wlabel("OLED_G", (30.48, 151.13), (-1, 0))
        s.text("SSD1306 module, pins GND VCC SCL SDA. Its own pull-ups\n"
               "hold SDA/SCL; Q1 cuts its supply when the meter is off.", (96.52, 147.32))

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                      fields=part("C601683", "TJ-S1615CY6TGLCCYRGB-A5", "TOGIALED"),
                      ref_at=(116.84, 171.45, None), val_at=(116.84, 189.23, None))
        s.connect(led, {"1": "+VSW"})
        for ref, val, net, pin, y, jog in (("R24", "680", "LED_R", "2", 170.18, 175.26),
                                           ("R25", "1k", "LED_G", "3", 180.34, None),
                                           ("R26", "330", "LED_B", "4", 190.5, 185.42)):
            r = self.R(ref, val, 93.98, y, rot=90, nets={"1": net})
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
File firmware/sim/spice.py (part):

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R11 mid1 tap {r11}
C11 tap 0 47n
R12 tap vmid {r12}
* VMID: PA2 through R13 into R14, C12; sensed on PA1 through R15.
R13 en vmid {r13}
R14 vmid 0 {r14}
C12 vmid 0 1u
R15 vmid pa1 1k
ILK1 pa1 0 {ileak}
* PA4 (TC): clamps to VDD and GND, leakage.
DPA4H tap vdd DPIN
DPA4L 0 tap DPIN
ILK4 tap 0 {ileak}

* Ohms, low range: PA6 through R16 to E_LO, R17 to the input.
R16 lo elo {r16}
R17 elo inohm {r17}
D2A 0 elo DBAV199
D2B elo batt DBAV199
R18 elo pa0 {r18}
DPA0H pa0 vdd DPIN
DPA0L 0 pa0 DPIN
ILK0 pa0 0 {ileak}
DPA6L 0 lo DPIN
* High range: PA3 through R19 to E_HI, R20 to the input.
R19 hi ehi 1k
R20 ehi inohm {r20}
D3A 0 ehi DBAV199
D3B ehi batt DBAV199
DPA3L 0 hi DPIN
* The input, through R21 into the C13 hold capacitor on PA5 (TC).
R21 inohm pa5 {r21}
C13 pa5 0 22n
DPA5H pa5 vdd DPIN
DPA5L 0 pa5 DPIN
ILK5 pa5 0 {ileak}
"""


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        return data


PROBES = ("v(tap)", "v(pa1)", "v(pa0)", "v(pa5)", "v(elo)", "v(ehi)", "v(inohm)",
          "i(vbat)", "i(vdd)", "i(vdut)")


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    rows = []
    for i in range(-140, 141):
        vin = i * 0.25
        d = op(netlist(vmid_en=True, v_in=vin, ileak=ileak), ("v(tap)", "v(pa1)", "i(vdd)"))
        rows.append({"vin": vin, "tap": d["v(tap)"], "vmid": d["v(pa1)"], "i_vdd": d["i(vdd)"]})
    write(f"volts{tag}.csv", rows)


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    for rx in [0.0] + decades(0.1, 30e6, 12):
        dut = ("r", max(rx, 1e-6))
        for drive in ("lo", "hi"):
            d = op(netlist(drive=drive, dut=dut, ileak=ileak), ("v(pa0)", "v(pa5)", "v(elo)", "v(inohm)"))
            rows.append({"rx": rx, "range": drive, "elo": d["v(pa0)"], "input": d["v(pa5)"],
                         "node_elo": d["v(elo)"], "node_in": d["v(inohm)"]})
    write(f"ohms{tag}.csv", rows)

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def diode_cases():
    rows = []
    for name, model in (("1N4148", "D1N4148"), ("red LED", "DLEDRED")):
        d = op(netlist(drive="lo", dut=("d", model)), ("v(pa0)", "v(pa5)", "v(inohm)", "i(vlo)"))
        rows.append({"part": name, "elo": d["v(pa0)"], "input": d["v(pa5)"], "vf": d["v(inohm)"],
                     "i_test": -d["i(vlo)"]})
    write("diode.csv", rows)

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    """A voltage source on the ohms input, with the low range driving (worst
    case: firmware has not noticed yet) and with both drives off."""
    rows = []
    probes = ("v(pa0)", "v(pa5)", "v(elo)", "v(ehi)", "i(vbat)", "i(vdd)", "i(vdut)", "v(lo)")
    for i in range(-40, 41):
        vext = i * 1.0
        for drive in ("lo", None):
            d = op(netlist(drive=drive, dut=("v", vext)), probes)
            # Current into the battery through D2B/D3B, and into the 3.0 V rail.
            rows.append({"vext": vext, "drive": drive or "off", "pa0": d["v(pa0)"], "pa5": d["v(pa5)"],
                         "elo": d["v(elo)"], "ehi": d["v(ehi)"], "i_batt": -d["i(vbat)"],
                         "i_vdd": -d["i(vdd)"], "i_input": -d["i(vdut)"],
                         "p_r17": (vext - d["v(elo)"]) ** 2 / 10e3})
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    net = netlist(drive="lo", dut=None).replace("RDUT inohm 0 1T\n", "")
    net += "SW1 inohm 0 ctl 0 SWMOD\nVCTL ctl 0 PULSE(0 1 20m 1u 1u 100m 1)\n"
    net += ".model SWMOD SW(RON=0.05 ROFF=1T VT=0.5 VH=0.1)\n"
    ctl = "tran 50u 200m\nwrdata trans.txt v(pa5) v(pa0)\n"
    with tempfile.TemporaryDirectory() as d:
        cir = Path(d) / "c.cir"
        cir.write_text(net + ".ic v(pa5)=2.99\n.control\n" + ctl + ".endc\n.end\n")
        subprocess.run(["ngspice", "-b", str(cir)], capture_output=True, text=True, cwd=d, check=True)
        rows = []
        for line in (Path(d) / "trans.txt").read_text().split("\n"):
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    net = netlist(vmid_en=True).replace("VIN inv 0 DC 0.0\n", "VIN inv 0 PULSE(0 10 10m 1u 1u 1 2)\n")
    with tempfile.TemporaryDirectory() as d:
        cir = Path(d) / "c.cir"
        cir.write_text(net + ".control\ntran 100u 300m\nwrdata st.txt v(tap) v(pa1)\n.endc\n.end\n")
        subprocess.run(["ngspice", "-b", str(cir)], capture_output=True, text=True, cwd=d, check=True)
        rows = []
        for line in (Path(d) / "st.txt").read_text().split("\n"):
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        vext = float(i)
        row = {"vext": vext}
        for clamp in (False, True):
            d = op(netlist(dut=("v", vext), asleep=True, clamp=clamp), ("v(vdd)", "i(vbat)", "v(pa5)"))
            key = "clamp" if clamp else "noclamp"
            row[f"vdd_{key}"] = d["v(vdd)"]
            row[f"pa5_{key}"] = d["v(pa5)"]
        rows.append(row)
    write("stop_rail.csv", rows)

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    for s in range(n):
        vals = {k: v * (1 + rng.uniform(-1, 1) * TOLERANCE.get(k, 0.01)) for k, v in NOMINAL.items()}
        for vin in (-30.0, -10.0, -1.0, 0.0, 1.0, 5.0, 10.0, 20.0, 30.0):
            d = op(netlist(vmid_en=True, v_in=vin, values=vals), ("v(tap)", "v(pa1)"))
            vrows.append({"sample": s, "vin": vin, "tap": d["v(tap)"], "vmid": d["v(pa1)"]})
        for rx in (0.0, 1.0, 10.0, 100.0, 1e3, 10e3, 100e3, 1e6, 10e6):
            for drive in ("lo", "hi"):
                d = op(netlist(drive=drive, dut=("r", max(rx, 1e-6)), values=vals), ("v(pa0)", "v(pa5)"))
                orows.append({"sample": s, "rx": rx, "range": drive, "elo": d["v(pa0)"], "input": d["v(pa5)"]})
    write("mc_volts.csv", vrows)
    write("mc_ohms.csv", orows)

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
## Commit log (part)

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2024-07-21 added schematic and pcb files
2024-07-21 directory structure change
2024-07-21 Revert "directory structure change"
    This reverts commit aa9815be2f0c9639624ed1b2c933063fcc6c1c88.
2024-07-21 file name changes
2024-07-28 Create workflow to export images for diff.
2024-07-28 Fixed workflow typo.
2024-07-28 Fixed runner-dependent environment bug.
    The runner that executes the kicad-cli commands needs to be the same runner that installed KiCAD.
2024-07-28 Removed PCB diff export.
    Doesn't work yet and we don't even have a PCB so we'll just diff schematics for now.
2024-07-28 Update create_diff.yml
    Completely redesigned autodiff workflow.
2024-07-29 Added docs folder and BOM csv.
2024-07-29 Created kicad_diff directory for storing kicad_diff images.
2024-07-29 Moved svg diffs to docs/kicad_diffs
2024-07-29 Made placeholder diff to create kicad_diff directory
2024-07-29 Added microcontroller to BOM
2024-07-30 Added oscillator (TLC555CDR) to BOM csv
2024-07-30 Added piezo driver oscillator (based on TLC555CDR) to schematic. Needs component values calculated for oscillator parameters (frequency, etc).
2024-07-31 saving work
2024-08-01 test2
2024-08-01 UPDATE SKETCH FILE
2024-08-01 test
2024-08-01 Upload Schematic Files
2024-08-16 Added filter capacitors and reset button.
2024-08-16 Added back accidentally removed oscillator values.
2024-08-16 Added boot configuration jumper (default low) and I2C connector.
2024-08-31 Added temperature sensor to schematic and added .gitignore file.
2024-10-11 Added OLED footprint
2024-10-11 Added piezo buzzer and control circuitry.
2024-10-13 Completed PCB and some edits to schematic.
2024-10-13 Merged with working branch. PCB completed and introduced PCB diff functionality in create_diff.yml.
2024-10-13 Update silkscreen reference placements.
2024-10-13 Added silkscreen signature and revision number.
2024-10-13 Updated BOM.
2024-10-13 Final commit before sending off to JLC.
2024-10-15 Changed vias to 0.7 hole diameter and 0.9 diameter.
2024-10-16 Added ground plane fill zone.
2024-11-10 Revision 2
2024-11-10 Using ground plane vias.
